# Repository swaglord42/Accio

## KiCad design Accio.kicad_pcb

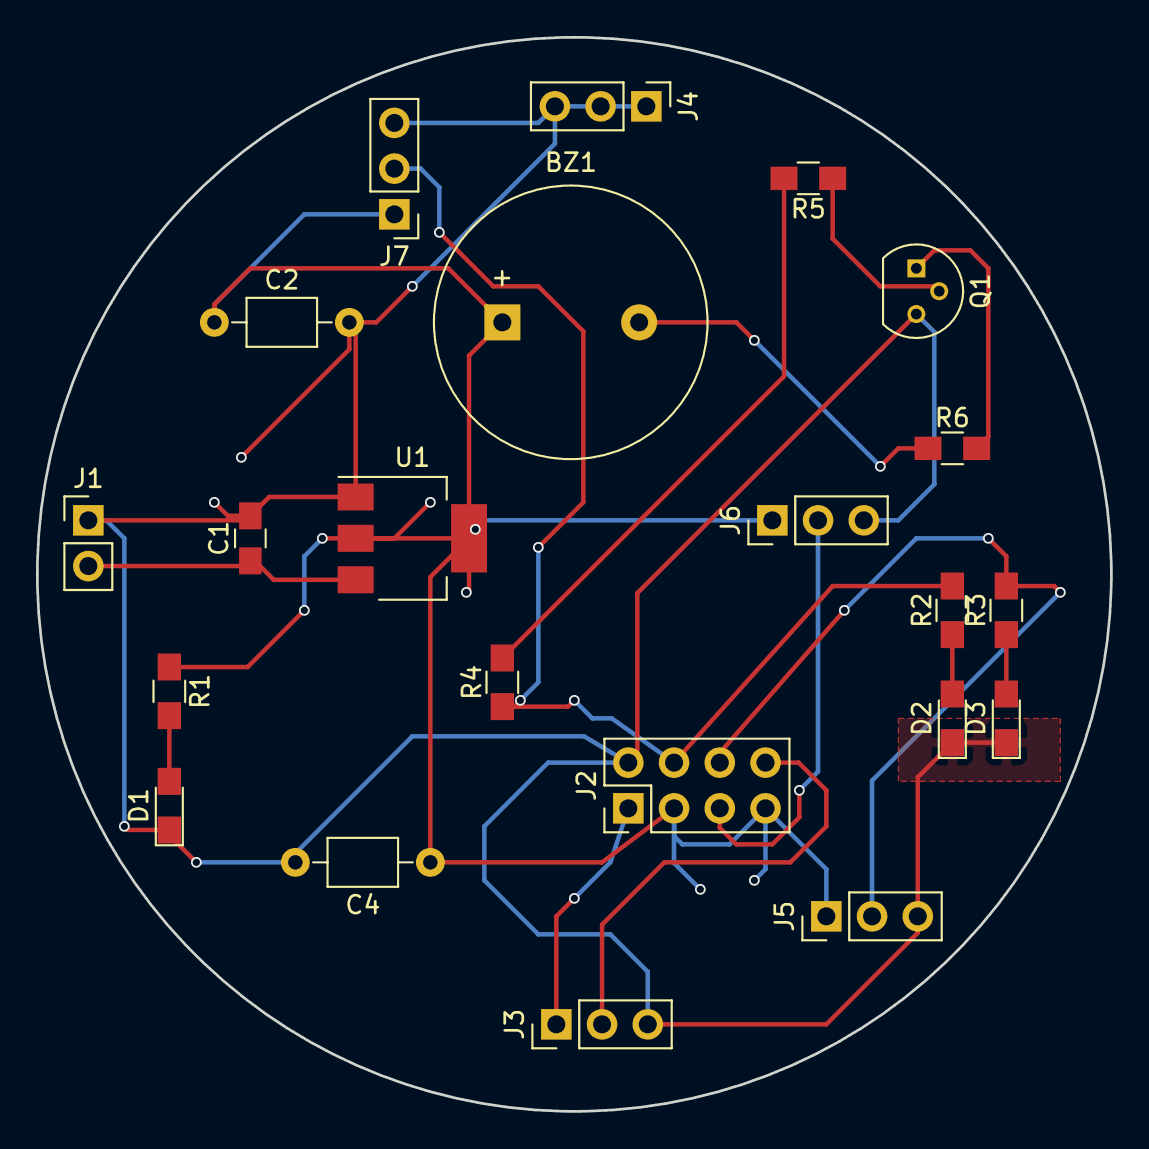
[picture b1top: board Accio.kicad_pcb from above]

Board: 2 copper layers, 59.7 x 59.7 mm, 22 parts (0 on the bottom side), 15 nets.

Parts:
BZ1: Buzzer; Buzzer_15x7.5RM7.6
C1: 10u; C_0805_HandSoldering
C2: 100u; C_Axial_L3.8mm_D2.6mm_P7.50mm_Horizontal
C4: 470u; C_Axial_L3.8mm_D2.6mm_P7.50mm_Horizontal
D1, D2, D3: LED; LED_0805_HandSoldering
J1: Conn_01x02; Pin_Header_Straight_1x02_Pitch2.54mm
J2: Conn_02x04_Odd_Even; Pin_Header_Straight_2x04_Pitch2.54mm
J3, J4, J5, J6, J7: Conn_01x03; Pin_Header_Straight_1x03_Pitch2.54mm
Q1: BC547; TO-92_Molded_Narrow
R1, R2, R3: 330; R_0805_HandSoldering
R4: 0; R_0805_HandSoldering
R5: 1k; R_0805_HandSoldering
R6: 100; R_0805_HandSoldering
U1: LM1117-3.3; SOT-223-3_TabPin2

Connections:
/ESP_RX: J2.8, J3.2
/ESP_TX: J2.1, J3.1
/GPIO0: J2.6, J5.2, R3.2
/GPIO2: J2.4, J7.2, R2.2, R4.1
/Reset: J2.5, J6.2
/Vdd_ESP: BZ1.1, C2.1, C4.1, J2.3, J2.7, J5.1, J6.1, J7.1, R1.1, U1.2
GND: C1.2, C2.2, C4.2, D1.1, D2.1, D3.1, J1.1, J2.2, J3.3, J4.1, J4.2, J4.3, J5.3, J6.3, J7.3, Q1.3, U1.1
unnamed: BZ1.2, R6.1
unnamed: C1.1, J1.2, U1.3
unnamed: D1.2, R1.2
unnamed: D2.2, R2.1
unnamed: D3.2, R3.1
unnamed: Q1.1, R6.2
unnamed: Q1.2, R5.1
unnamed: R4.2, R5.2
